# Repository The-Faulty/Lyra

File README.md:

# Lyra

**A SamD21 Based Rocket Deployment Altimeter**

This altimeter will be able to be used for single deployment events in mid to high power rocketry. A compact design was emphasized in order to allow for use in 24mm and larger body tubes, or attached to the parachute for a cable cutter or similar deployment method.

## Current State

As of right now, I am working on flight software with basic functionality. The original PCB design is filled with many flaws, however, I still included them for use as a reference. Plans have been made for a new version of the PCB to fix many, if not all, of the shortcomings my original design had. I believe I have found most of them, but one includes the difficulty of updating firmware and testing, which will inevitably lead to something being overlooked. Also to come are some pictures of the one prototype board that I have assembled. The changelog below is more to keep track of what I have or haven't tackled yet, so feel free to ignore it.

I have now successfully uploaded a version of the code to a Lyra board. One thing I did was replace the buzzer on the board with a bodged LED. This will allow for silent debugging and a guarantee that the lines are working. *This is the purpose of any digital writes to the buzzer pin.* The code that I uploaded ran until it attempted connection with the barometer in the setup. I will look further into the issue at a later point in time.

## The Bad, the Worse, and the Annoying

During my initial development of the Lyra pcb, I made some naive choices in terms of design, and overlooked other quality of life aspects which have led to many headaches during development. I'm going to go into some of the things that I have identified as issues in the current design or things I want to add in the next one.

The biggest issue that I made in the design of this pcb was not using a USB port. I figured that as long as I had the SWD I would be fine, but it just complicates development because I can't have the flash and SD card board attached at the same time. Another issue is lack of physical indicators. having LEDs on the power lines, pyro lines, and just attached to a GPIO pin would have helped a lot in diagnosing issues. Instead of using the BMP388, a barometer that I have used before and knew worked, I chose the MS5607 for Lyra. I don't remember why I made that choice, but the MS5607 has a few downsides compared to the BMP388. For one, there is no data ready register. This means that your code has to blindly wait for the reading to be completed, and then check back after. The libraries for using this sensor are also less tested than those for the BMP388. I also did not think very hard about the use of Lyra during an actual launch. I planned for the code to read a settings file from the SD card at launch, however, if I planned on using Lyra in multiple rockets or adjust settings on the go, I would have to bring a laptop. On the next itteration, one solution would be to use an oled shield, such as the adafruit feather oled, with a simple menu system for settings and readout. Finally, I wish I had broken out more pins to the daughter pcb. I didn't use all of the pins on the connector, and could have broken out I2C lines or similar for further prototyping.

## Changelog

Latest Changes:

**V0.2 - "Hands up, Don't Chute!"**

Notes: I think that most of the program is here, just need to do the loop logic. I also want to add data logging to the start of the flight.

- Fixed typo of `stateMacine` to `stateMachine`
- Fixed `state` being initialized as an integer instead of an instance of the `stateMachine` enum
- Fixed lack of function prototypes

- Changed `loop()` to use switch/case instead of `if else`
- Moved `readAlt()` to the start of if statement instead of in each case

- Added `ISDROGUE` and `ISAPOGEEDEPLOY` to user variables (I missed them in the last update)
- Added `DEPLOYALT` variable for setting the deployment altitude
- Added `SAVEDATA` boolean to toggle saving data to flash
- Added use of buzzer in `setup()` for indicating barometer found and setup complete
- Added `landed` case to `loop()`
- Added `rollPeriod` and `rollVelo` for use in velocity and acceleration calculations
- Added `calcAccel` for acceleration

**V0.1 - "No Function Junction"**

- Fixed variables being logged being out of order
- Fixed barometer code to use correct barometer model
- Fixed `readAlt()` function's for loop running until greater than the array's index
- Fixed not changing state from `startUp` to `idle` in setup

- Removed variable `rateLeng` and instead directly used the `rollAvg` array for vertical speed calculation

- Changed user-defined variables to be under define tags to allow usage in declaring array lengths

- Added vertical speed function (`getRate()`) and `avgRate` variable
- Added battery voltage function (`getBattVoltage()`)
- Added vertical speed to logging data
- Added `period` and `lastMillis` variables for tracking loop cycles
- Added majority of this ReadMe

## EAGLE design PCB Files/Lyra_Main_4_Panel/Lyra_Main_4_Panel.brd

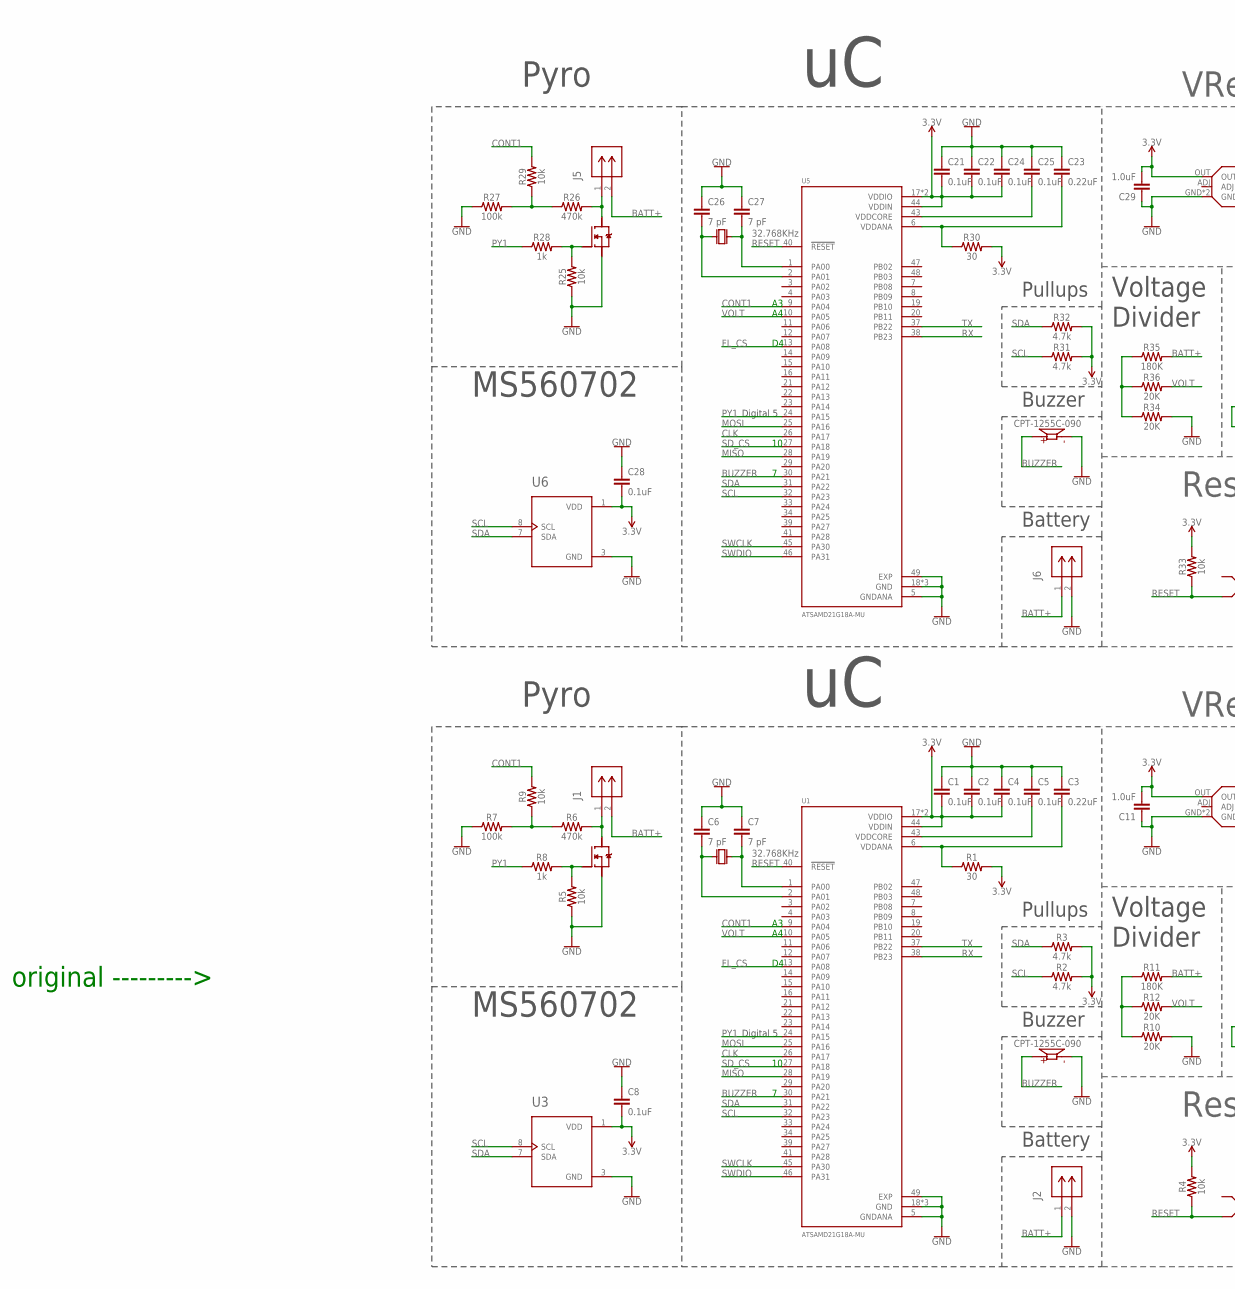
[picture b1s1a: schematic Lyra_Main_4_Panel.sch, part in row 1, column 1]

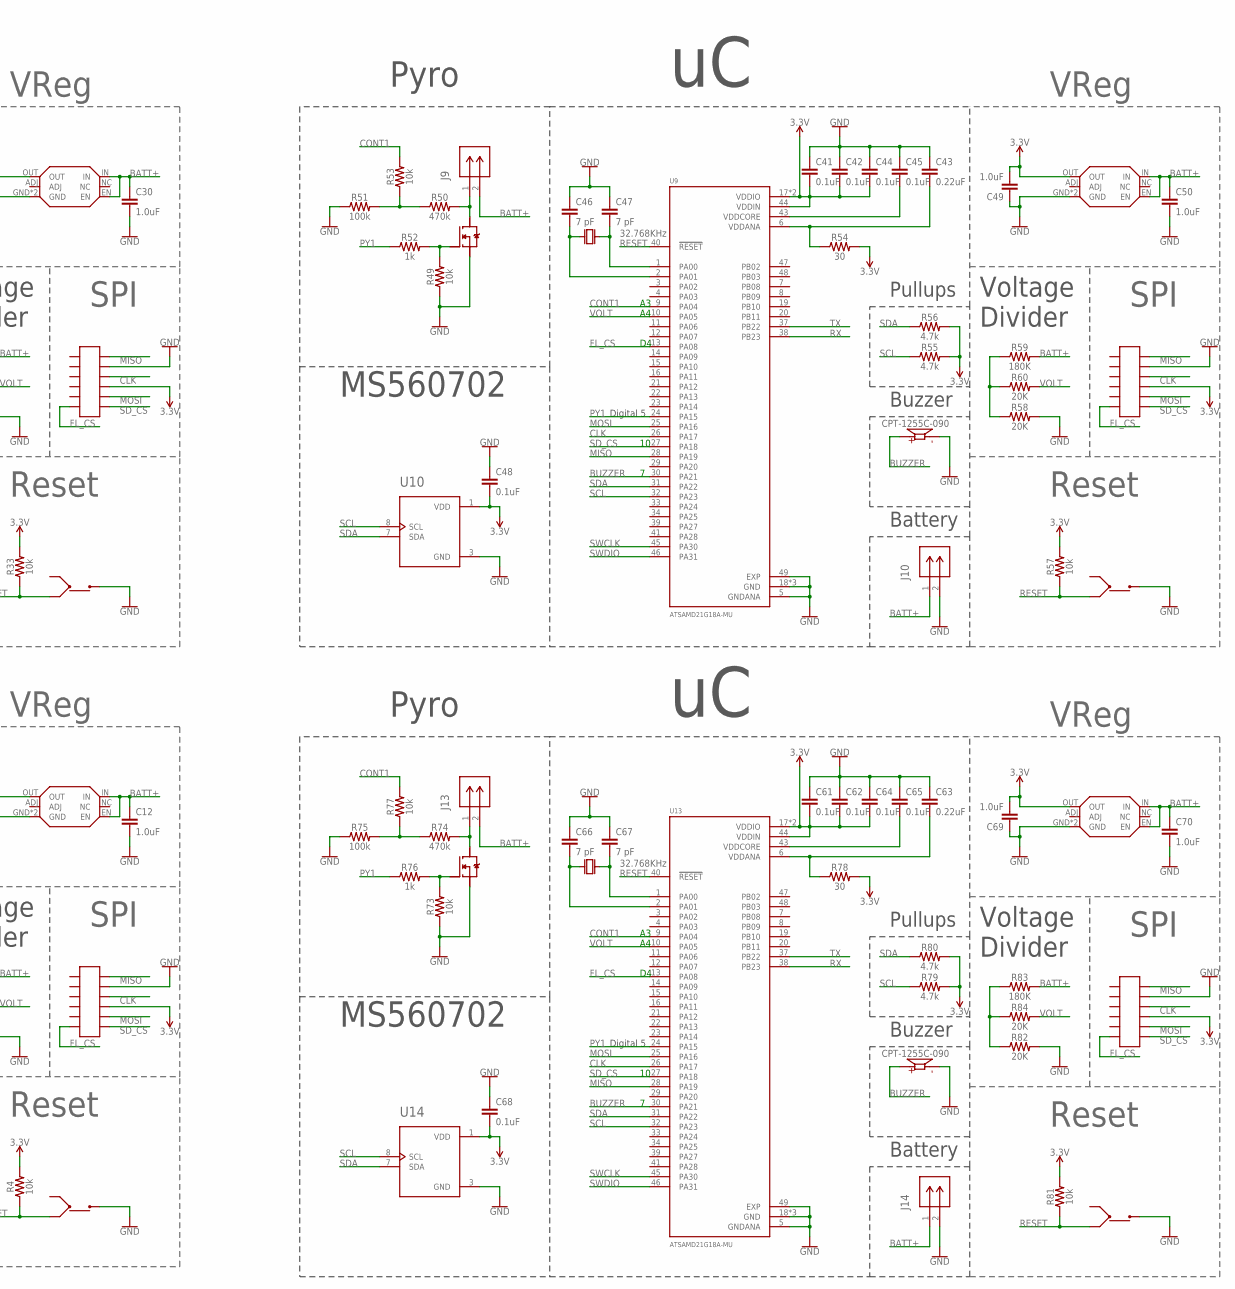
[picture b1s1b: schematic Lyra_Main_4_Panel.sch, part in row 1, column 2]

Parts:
C1, C2, C4, C5, C8, C21, C22, C24, C25, C28, C41, C42, C44, C45, C48, C61, C62, C64, C65, C68: 0.1uF; 0603
C3, C23, C43, C63: 0.22uF; 0603
C6, C7, C26, C27, C46, C47, C66, C67: 7 pF; 0402
C11, C12, C29, C30, C49, C50, C69, C70: 1.0uF; 0402
J1, J2, J5, J6, J9, J10, J13, J14: OSTVN02A150; CONN_OSTVN02A150_OST
LS2, LS3, LS5, LS7: CPT-1255C-090; CUI_CPT-1255C-090
R1, R30, R54, R78: 30; 0402
R2, R3, R31, R32, R55, R56, R79, R80: 4.7k; 0603
R4, R5, R9, R25, R29, R33, R49, R53, R57, R73, R77, R81: 10k; 0402
R6, R26, R50, R74: 470k; 0402
R7, R27, R51, R75: 100k; 0402
R8, R28, R52, R76: 1k; 0402
R10, R12, R34, R36, R58, R60, R82, R84: 20K; 0402
R11, R35, R59, R83: 180K; 0402
U1, U5, U9, U13: ATSAMD21G18A-MU; QFN50P700X700X90-49N
U3, U6, U10, U14: MS860702BA01-50; TE_MS860702BA01-50
U$1, U$12, U$22, U$32: 32.768KHz; FC-135
U$2, U$11, U$21, U$31: IRLHM630PBF
U$3, U$13, U$23, U$33: NCP718AMT330TBG; NCP718BMT330TBG
U$4, U$14, U$24, U$34: BUTTON
U$5, U$15, U$25, U$35: 12POS_SOCKET

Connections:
3.3V: C1.2, C2.2, C4.2, C8.2, C11.2, C21.2, C22.2, C24.2, C28.2, C29.2, C41.2, C42.2, C44.2, C48.2, C49.2, C61.2, C62.2, C64.2, C68.2, C69.2, R1.2, R2.2, R3.2, R4.2, R30.2, R31.2, R32.2, R33.2, R54.2, R55.2, R56.2, R57.2, R78.2, R79.2, R80.2, R81.2, U1.17 (VDDIO), U1.36 (VDDIO), U1.44 (VDDIN), U3.1 (VDD), U5.17 (VDDIO), U5.36 (VDDIO), U5.44 (VDDIN), U6.1 (VDD), U9.17 (VDDIO), U9.36 (VDDIO), U9.44 (VDDIN), U10.1 (VDD), U13.17 (VDDIO), U13.36 (VDDIO), U13.44 (VDDIN), U14.1 (VDD), U$3.OUT, U$5.P$9, U$13.OUT, U$15.P$9, U$23.OUT, U$25.P$9, U$33.OUT, U$35.P$9
BATT+: C12.1, C30.1, C50.1, C70.1, J1.2, J2.1, J5.2, J6.1, J9.2, J10.1, J13.2, J14.1, R11.2, R35.2, R59.2, R83.2, U$3.EN, U$3.IN, U$13.EN, U$13.IN, U$23.EN, U$23.IN, U$33.EN, U$33.IN
BUZZER: LS2.P, LS3.P, LS5.P, LS7.P, U1.30 (PA21), U5.30 (PA21), U9.30 (PA21), U13.30 (PA21)
CLK: U1.26 (PA17), U5.26 (PA17), U9.26 (PA17), U13.26 (PA17), U$5.P$10, U$15.P$10, U$25.P$10, U$35.P$10
CONT1: R9.2, R29.2, R53.2, R77.2, U1.9 (PA04), U5.9 (PA04), U9.9 (PA04), U13.9 (PA04)
FL_CS: U1.13 (PA08), U5.13 (PA08), U9.13 (PA08), U13.13 (PA08), U$5.P$6, U$15.P$6, U$25.P$6, U$35.P$6
GND: C1.1, C2.1, C3.1, C4.1, C5.1, C6.1, C7.1, C8.1, C11.1, C12.2, C21.1, C22.1, C23.1, C24.1, C25.1, C26.1, C27.1, C28.1, C29.1, C30.2, C41.1, C42.1, C43.1, C44.1, C45.1, C46.1, C47.1, C48.1, C49.1, C50.2, C61.1, C62.1, C63.1, C64.1, C65.1, C66.1, C67.1, C68.1, C69.1, C70.2, J2.2, J6.2, J10.2, J14.2, LS2.N, LS3.N, LS5.N, LS7.N, R5.1, R7.1, R10.2, R25.1, R27.1, R34.2, R49.1, R51.1, R58.2, R73.1, R75.1, R82.2, U1.5 (GNDANA), U1.18 (GND), U1.35 (GND), U1.42 (GND), U1.49 (EXP), U3.3 (GND), U5.5 (GNDANA), U5.18 (GND), U5.35 (GND), U5.42 (GND), U5.49 (EXP), U6.3 (GND), U9.5 (GNDANA), U9.18 (GND), U9.35 (GND), U9.42 (GND), U9.49 (EXP), U10.3 (GND), U13.5 (GNDANA), U13.18 (GND), U13.35 (GND), U13.42 (GND), U13.49 (EXP), U14.3 (GND), U$2.P$2, U$2.P$3, U$2.P$4, U$3.GND, U$3.P$7 (GND), U$4.4 (OUT), U$5.P$11, U$11.P$2, U$11.P$3, U$11.P$4, U$13.GND, U$13.P$7 (GND), U$14.4 (OUT), U$15.P$11, U$21.P$2, U$21.P$3, U$21.P$4, U$23.GND, U$23.P$7 (GND), U$24.4 (OUT), U$25.P$11, U$31.P$2, U$31.P$3, U$31.P$4, U$33.GND, U$33.P$7 (GND), U$34.4 (OUT), U$35.P$11
MISO: U1.28 (PA19), U5.28 (PA19), U9.28 (PA19), U13.28 (PA19), U$5.P$12, U$15.P$12, U$25.P$12, U$35.P$12
MOSI: U1.25 (PA16), U5.25 (PA16), U9.25 (PA16), U13.25 (PA16), U$5.P$8, U$15.P$8, U$25.P$8, U$35.P$8
unnamed: C7.2, U1.1 (PA00), U$1.P$2
unnamed: J1.1, R6.2, U$2.P$5, U$2.P$6, U$2.P$7, U$2.P$8, U$2.P$9
unnamed: R5.2, R8.2, U$2.P$1
unnamed: C6.2, U1.2 (PA01), U$1.P$1
unnamed: R6.1, R7.2, R9.1
unnamed: R10.1, R11.1, R12.1
unnamed: C5.2, U1.43 (VDDCORE)
unnamed: C3.2, R1.1, U1.6 (VDDANA)
unnamed: J5.1, R26.2, U$11.P$5, U$11.P$6, U$11.P$7, U$11.P$8, U$11.P$9
unnamed: R25.2, R28.2, U$11.P$1
unnamed: R26.1, R27.2, R29.1
unnamed: C27.2, U5.1 (PA00), U$12.P$2
unnamed: C26.2, U5.2 (PA01), U$12.P$1
unnamed: C25.2, U5.43 (VDDCORE)
unnamed: C23.2, R30.1, U5.6 (VDDANA)
unnamed: R34.1, R35.1, R36.1
unnamed: J9.1, R50.2, U$21.P$5, U$21.P$6, U$21.P$7, U$21.P$8, U$21.P$9
unnamed: R49.2, R52.2, U$21.P$1
unnamed: R50.1, R51.2, R53.1
unnamed: C47.2, U9.1 (PA00), U$22.P$2
unnamed: C46.2, U9.2 (PA01), U$22.P$1
unnamed: C45.2, U9.43 (VDDCORE)
unnamed: C43.2, R54.1, U9.6 (VDDANA)
unnamed: R58.1, R59.1, R60.1
unnamed: J13.1, R74.2, U$31.P$5, U$31.P$6, U$31.P$7, U$31.P$8, U$31.P$9
unnamed: R73.2, R76.2, U$31.P$1
unnamed: R74.1, R75.2, R77.1
unnamed: C67.2, U13.1 (PA00), U$32.P$2
unnamed: C66.2, U13.2 (PA01), U$32.P$1
unnamed: C65.2, U13.43 (VDDCORE)
unnamed: C63.2, R78.1, U13.6 (VDDANA)
unnamed: R82.1, R83.1, R84.1
PY1: R8.1, R28.1, R52.1, R76.1, U1.24 (PA15), U5.24 (PA15), U9.24 (PA15), U13.24 (PA15)
RESET: R4.1, R33.1, R57.1, R81.1, U1.40 (!RESET), U5.40 (!RESET), U9.40 (!RESET), U13.40 (!RESET), U$4.2 (IN(2)), U$14.2 (IN(2)), U$24.2 (IN(2)), U$34.2 (IN(2))
RX: U1.38 (PB23), U5.38 (PB23), U9.38 (PB23), U13.38 (PB23)
SCL: R2.1, R31.1, R55.1, R79.1, U1.32 (PA23), U3.8 (SCL), U5.32 (PA23), U6.8 (SCL), U9.32 (PA23), U10.8 (SCL), U13.32 (PA23), U14.8 (SCL)
SDA: R3.1, R32.1, R56.1, R80.1, U1.31 (PA22), U3.7 (SDA), U5.31 (PA22), U6.7 (SDA), U9.31 (PA22), U10.7 (SDA), U13.31 (PA22), U14.7 (SDA)
SD_CS: U1.27 (PA18), U5.27 (PA18), U9.27 (PA18), U13.27 (PA18), U$5.P$7, U$15.P$7, U$25.P$7, U$35.P$7
SWCLK: U1.45 (PA30), U5.45 (PA30), U9.45 (PA30), U13.45 (PA30)
SWDIO: U1.46 (PA31), U5.46 (PA31), U9.46 (PA31), U13.46 (PA31)
TX: U1.37 (PB22), U5.37 (PB22), U9.37 (PB22), U13.37 (PB22)
VOLT: R12.2, R36.2, R60.2, R84.2, U1.10 (PA05), U5.10 (PA05), U9.10 (PA05), U13.10 (PA05)

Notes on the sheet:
Pyro
Buzzer
Battery
MS560702
Pullups
VReg
SPI
Reset
Digital 5
Voltage Divider
original --------->

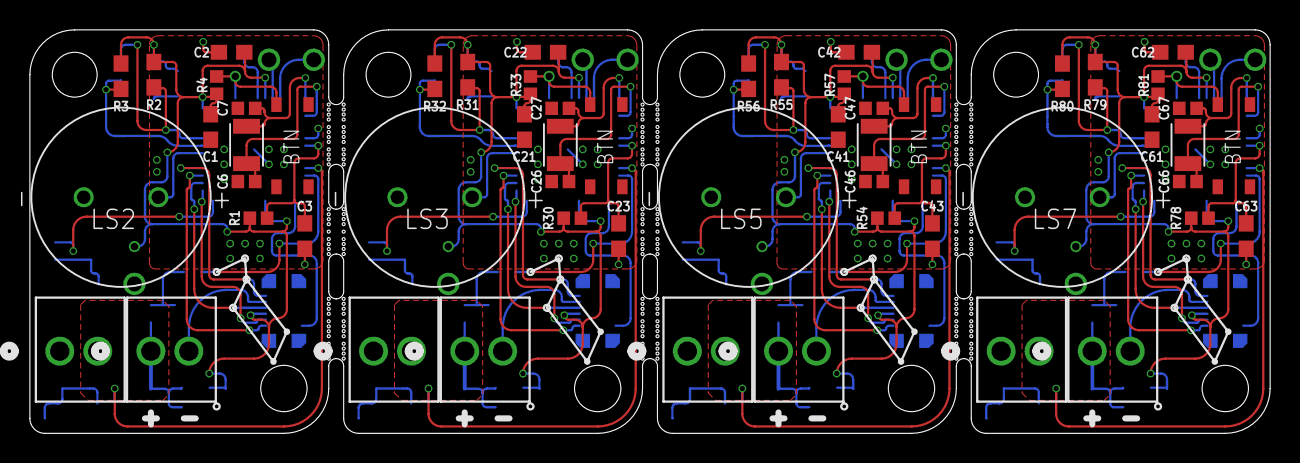
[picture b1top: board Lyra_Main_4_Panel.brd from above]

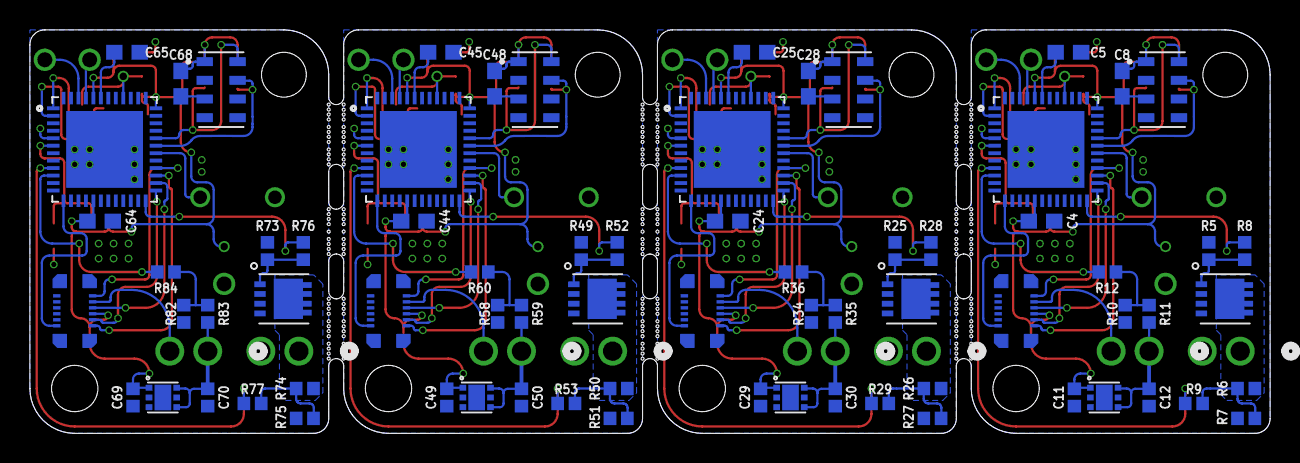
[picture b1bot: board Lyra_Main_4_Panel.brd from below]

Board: 2 copper layers, 83.0 x 27.0 mm, 128 parts (72 on the bottom side), 51 nets.

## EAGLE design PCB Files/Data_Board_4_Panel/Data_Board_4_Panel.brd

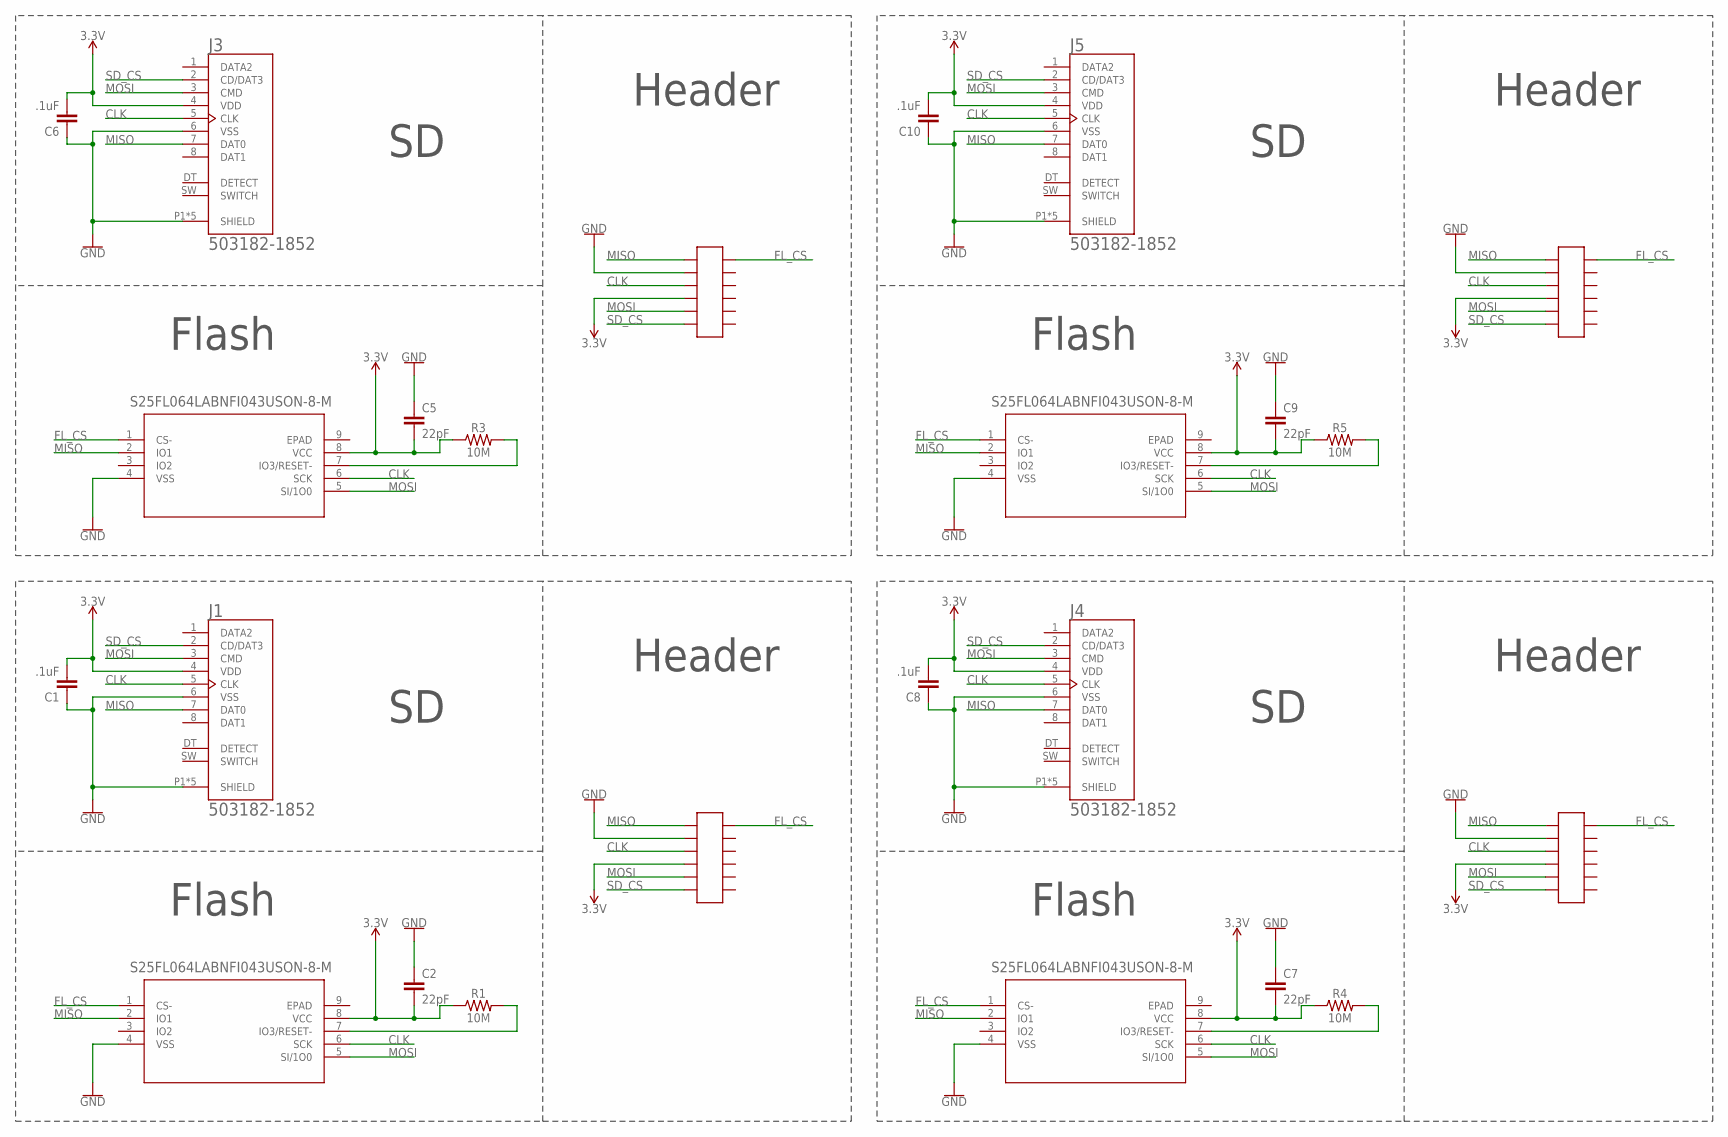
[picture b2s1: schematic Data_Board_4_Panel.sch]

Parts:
C1, C6, C8, C10: .1uF; 0603
C2, C5, C7, C9: 22pF; 0603
J1, J3, J4, J5: 503182-1852; MOLEX_503182-1852
R1, R3, R4, R5: 10M; 0603
U1, U3, U4, U5: S25FL064LABNFI043USON-8-M; USON-8-M
U$1, U$3, U$4, U$5: 12POS_HEADER

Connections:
3.3V: C1.2, C2.2, C5.2, C6.2, C7.2, C8.2, C9.2, C10.2, J1.4 (VDD), J3.4 (VDD), J4.4 (VDD), J5.4 (VDD), R1.1, R3.1, R4.1, R5.1, U1.8 (VCC), U3.8 (VCC), U4.8 (VCC), U5.8 (VCC), U$1.P$4, U$3.P$4, U$4.P$4, U$5.P$4
CLK: J1.5 (CLK), J3.5 (CLK), J4.5 (CLK), J5.5 (CLK), U1.6 (SCK), U3.6 (SCK), U4.6 (SCK), U5.6 (SCK), U$1.P$3, U$3.P$3, U$4.P$3, U$5.P$3
FL_CS: U1.1 (CS-), U3.1 (CS-), U4.1 (CS-), U5.1 (CS-), U$1.P$12, U$3.P$12, U$4.P$12, U$5.P$12
GND: C1.1, C2.1, C5.1, C6.1, C7.1, C8.1, C9.1, C10.1, J1.6 (VSS), J1.P1 (SHIELD), J1.P2 (SHIELD), J1.P3 (SHIELD), J1.P4 (SHIELD), J1.P5 (SHIELD), J3.6 (VSS), J3.P1 (SHIELD), J3.P2 (SHIELD), J3.P3 (SHIELD), J3.P4 (SHIELD), J3.P5 (SHIELD), J4.6 (VSS), J4.P1 (SHIELD), J4.P2 (SHIELD), J4.P3 (SHIELD), J4.P4 (SHIELD), J4.P5 (SHIELD), J5.6 (VSS), J5.P1 (SHIELD), J5.P2 (SHIELD), J5.P3 (SHIELD), J5.P4 (SHIELD), J5.P5 (SHIELD), U1.4 (VSS), U3.4 (VSS), U4.4 (VSS), U5.4 (VSS), U$1.P$2, U$3.P$2, U$4.P$2, U$5.P$2
MISO: J1.7 (DAT0), J3.7 (DAT0), J4.7 (DAT0), J5.7 (DAT0), U1.2 (IO1), U3.2 (IO1), U4.2 (IO1), U5.2 (IO1), U$1.P$1, U$3.P$1, U$4.P$1, U$5.P$1
MOSI: J1.3 (CMD), J3.3 (CMD), J4.3 (CMD), J5.3 (CMD), U1.5 (SI/1O0), U3.5 (SI/1O0), U4.5 (SI/1O0), U5.5 (SI/1O0), U$1.P$5, U$3.P$5, U$4.P$5, U$5.P$5
unnamed: R3.2, U3.7 (IO3/RESET-)
unnamed: R4.2, U4.7 (IO3/RESET-)
unnamed: R5.2, U5.7 (IO3/RESET-)
unnamed: R1.2, U1.7 (IO3/RESET-)
SD_CS: J1.2 (CD/DAT3), J3.2 (CD/DAT3), J4.2 (CD/DAT3), J5.2 (CD/DAT3), U$1.P$6, U$3.P$6, U$4.P$6, U$5.P$6

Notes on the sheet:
Flash
Header

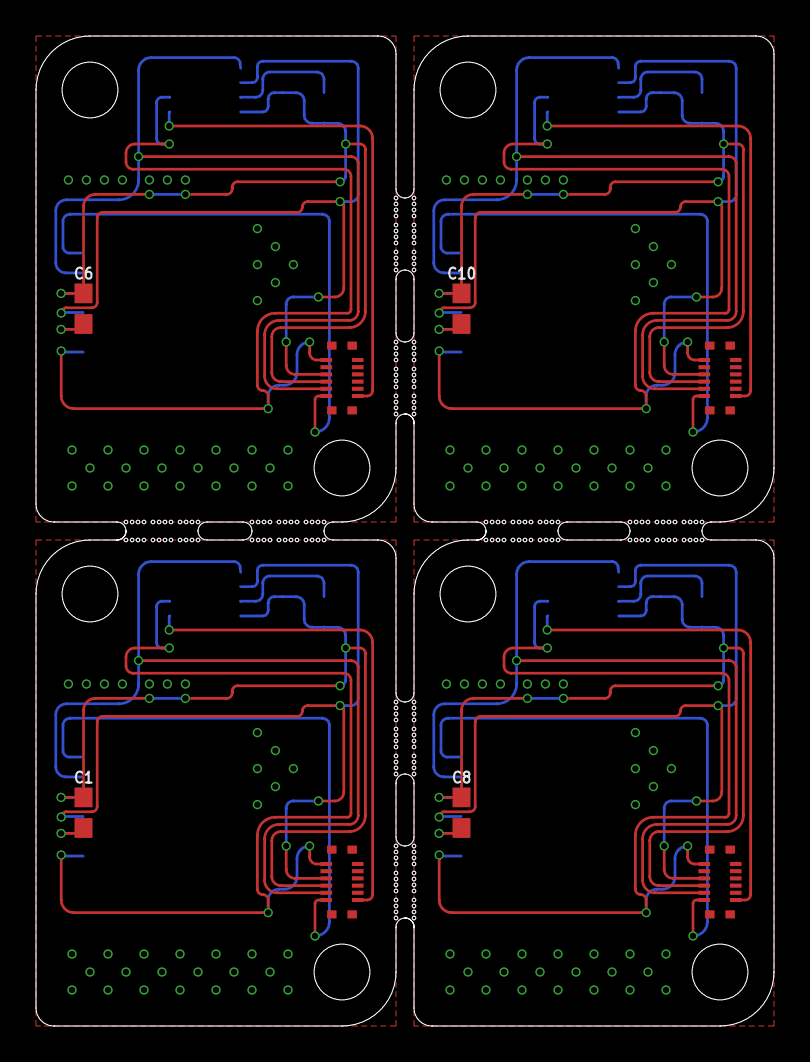
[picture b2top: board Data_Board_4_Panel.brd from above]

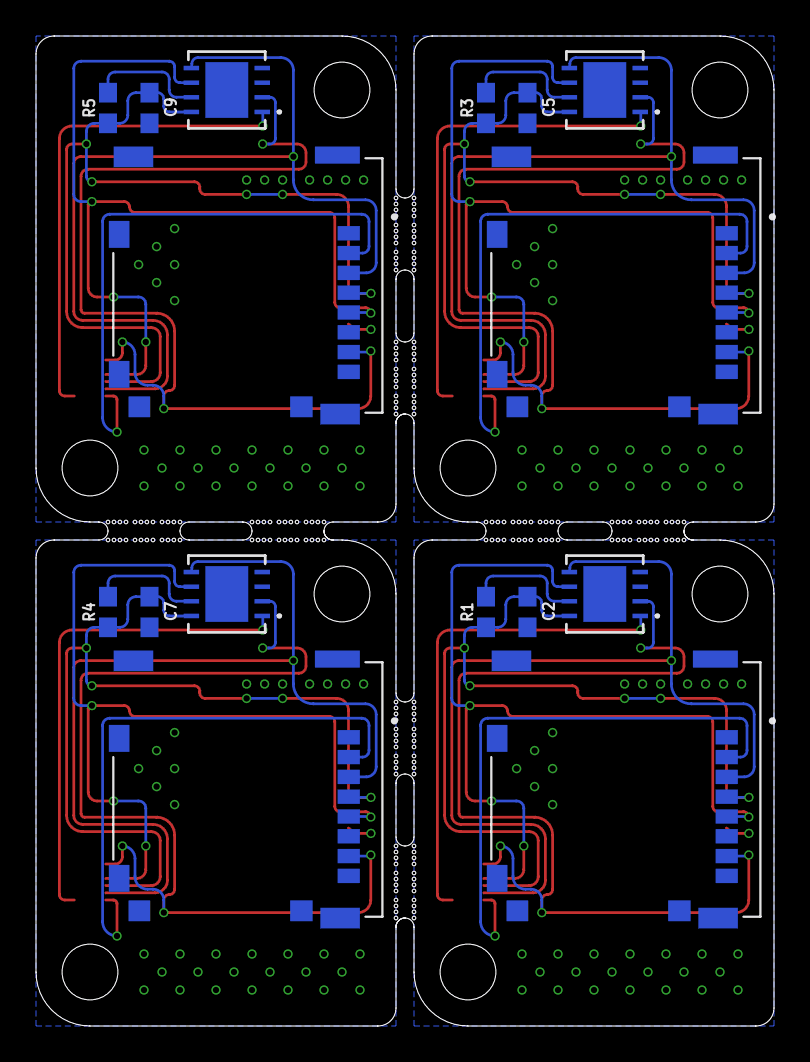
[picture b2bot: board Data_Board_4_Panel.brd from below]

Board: 2 copper layers, 41.0 x 55.0 mm, 24 parts (16 on the bottom side), 11 nets.

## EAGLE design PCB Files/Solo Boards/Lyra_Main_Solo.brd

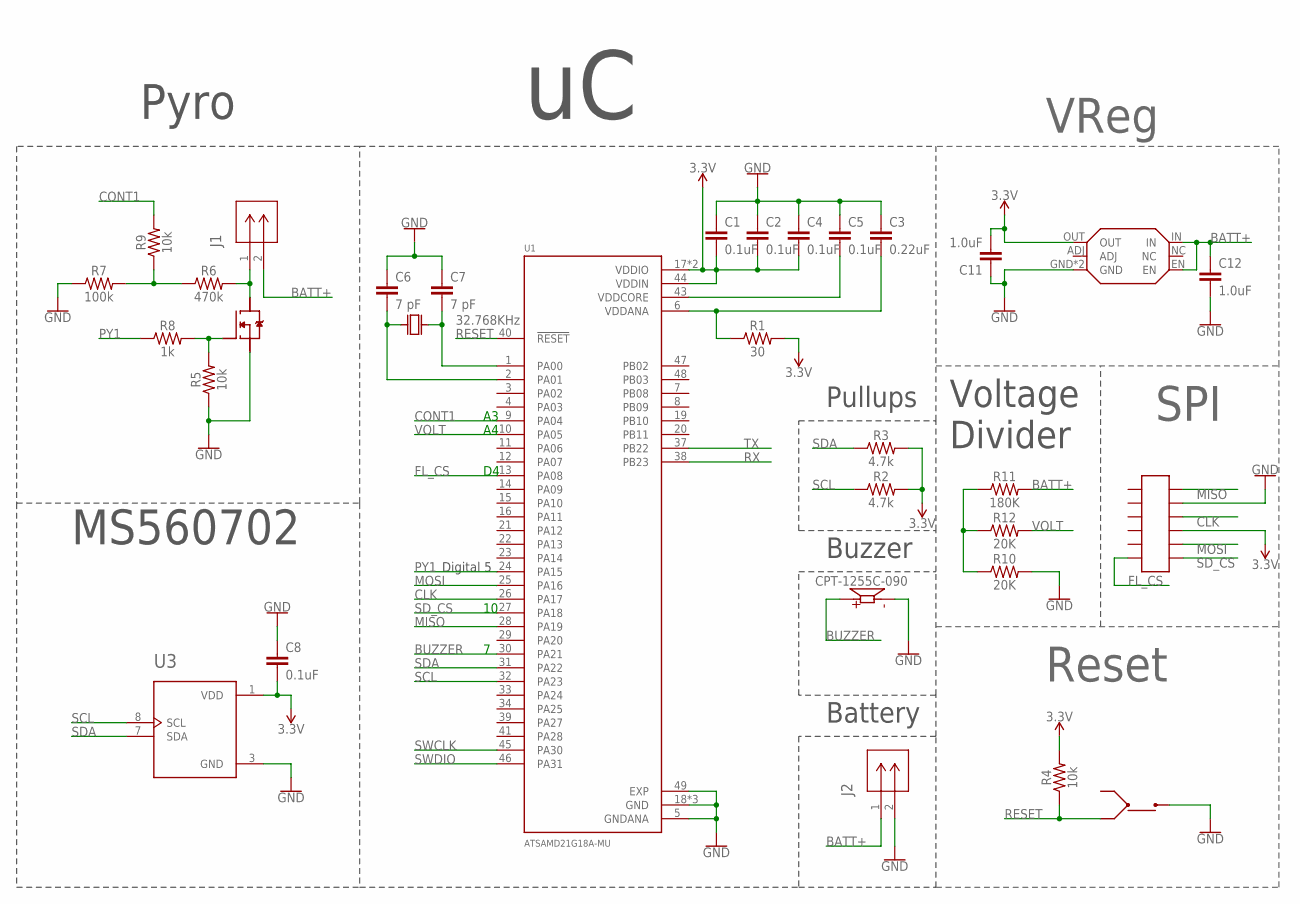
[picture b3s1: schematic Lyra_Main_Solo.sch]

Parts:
C1, C2, C4, C5, C8: 0.1uF; 0603
C3: 0.22uF; 0603
C6, C7: 7 pF; 0402
C11, C12: 1.0uF; 0402
J1, J2: OSTVN02A150; CONN_OSTVN02A150_OST
LS2: CPT-1255C-090; CUI_CPT-1255C-090
R1: 30; 0402
R2, R3: 4.7k; 0603
R4, R5, R9: 10k; 0402
R6: 470k; 0402
R7: 100k; 0402
R8: 1k; 0402
R10, R12: 20K; 0402
R11: 180K; 0402
U1: ATSAMD21G18A-MU; QFN50P700X700X90-49N
U3: MS860702BA01-50; TE_MS860702BA01-50
U$1: 32.768KHz; FC-135
U$2: IRLHM630PBF
U$3: NCP718AMT330TBG; NCP718BMT330TBG
U$4: BUTTON
U$5: 12POS_SOCKET

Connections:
3.3V: C1.2, C2.2, C4.2, C8.2, C11.2, R1.2, R2.2, R3.2, R4.2, U1.17 (VDDIO), U1.36 (VDDIO), U1.44 (VDDIN), U3.1 (VDD), U$3.OUT, U$5.P$9
BATT+: C12.1, J1.2, J2.1, R11.2, U$3.EN, U$3.IN
BUZZER: LS2.P, U1.30 (PA21)
CLK: U1.26 (PA17), U$5.P$10
CONT1: R9.2, U1.9 (PA04)
FL_CS: U1.13 (PA08), U$5.P$6
GND: C1.1, C2.1, C3.1, C4.1, C5.1, C6.1, C7.1, C8.1, C11.1, C12.2, J2.2, LS2.N, R5.1, R7.1, R10.2, U1.5 (GNDANA), U1.18 (GND), U1.35 (GND), U1.42 (GND), U1.49 (EXP), U3.3 (GND), U$2.P$2, U$2.P$3, U$2.P$4, U$3.GND, U$3.P$7 (GND), U$4.4 (OUT), U$5.P$11
MISO: U1.28 (PA19), U$5.P$12
MOSI: U1.25 (PA16), U$5.P$8
unnamed: C7.2, U1.1 (PA00), U$1.P$2
unnamed: J1.1, R6.2, U$2.P$5, U$2.P$6, U$2.P$7, U$2.P$8, U$2.P$9
unnamed: R5.2, R8.2, U$2.P$1
unnamed: C6.2, U1.2 (PA01), U$1.P$1
unnamed: R6.1, R7.2, R9.1
unnamed: R10.1, R11.1, R12.1
unnamed: C5.2, U1.43 (VDDCORE)
unnamed: C3.2, R1.1, U1.6 (VDDANA)
PY1: R8.1, U1.24 (PA15)
RESET: R4.1, U1.40 (!RESET), U$4.2 (IN(2))
RX: U1.38 (PB23)
SCL: R2.1, U1.32 (PA23), U3.8 (SCL)
SDA: R3.1, U1.31 (PA22), U3.7 (SDA)
SD_CS: U1.27 (PA18), U$5.P$7
SWCLK: U1.45 (PA30)
SWDIO: U1.46 (PA31)
TX: U1.37 (PB22)
VOLT: R12.2, U1.10 (PA05)

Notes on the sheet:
Pyro
Buzzer
Battery
MS560702
Pullups
VReg
SPI
Reset
Digital 5
Voltage Divider

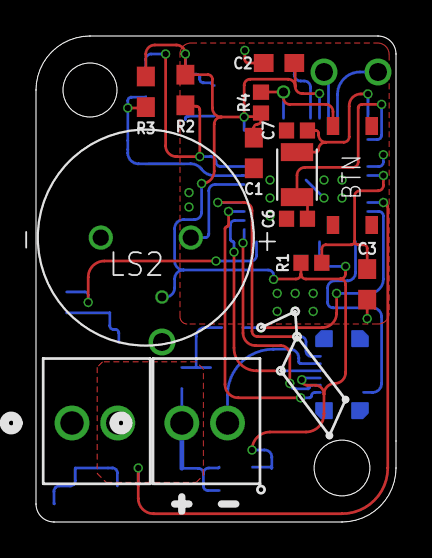
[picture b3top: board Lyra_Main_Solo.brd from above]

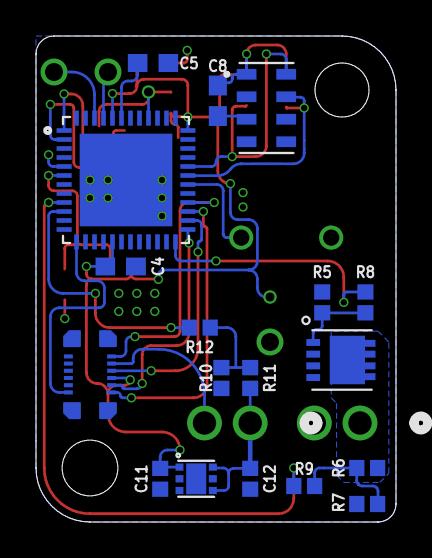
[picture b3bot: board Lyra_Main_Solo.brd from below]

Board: 2 copper layers, 20.0 x 27.0 mm, 32 parts (18 on the bottom side), 23 nets.

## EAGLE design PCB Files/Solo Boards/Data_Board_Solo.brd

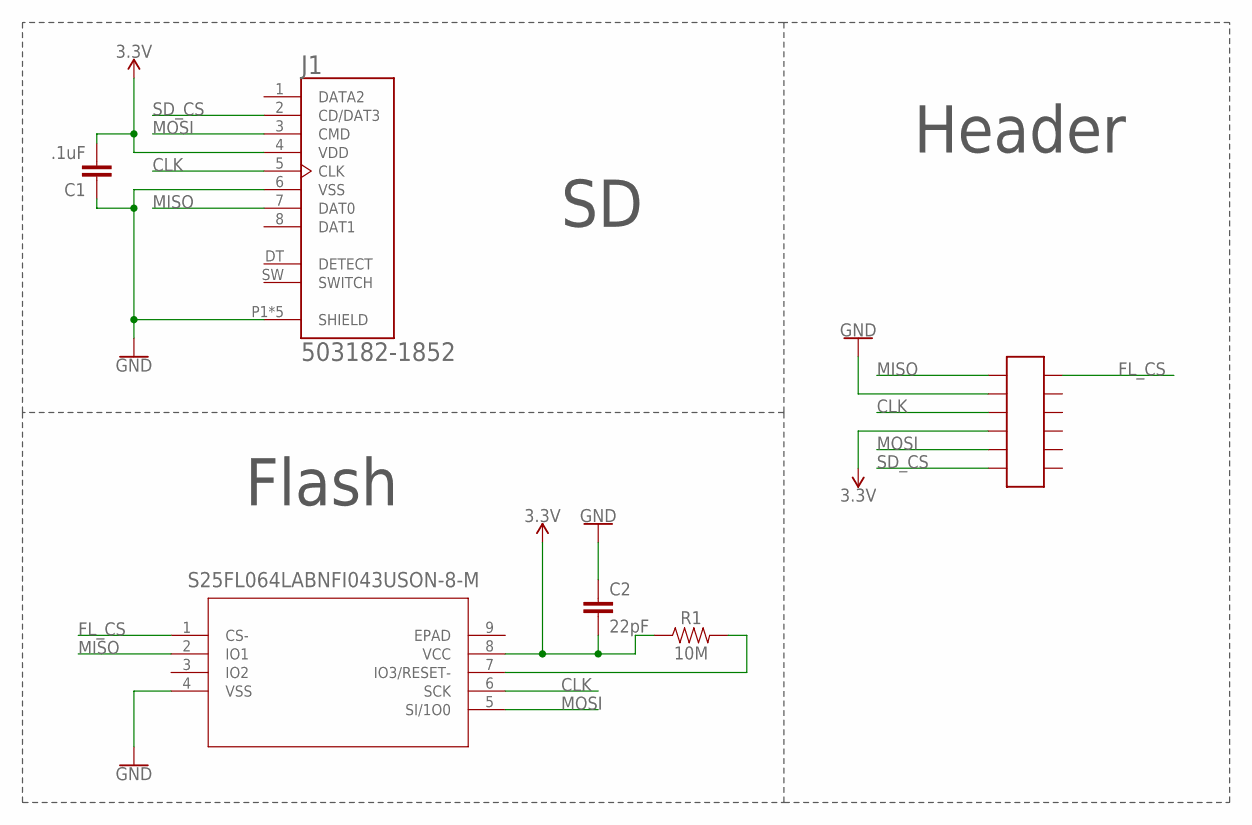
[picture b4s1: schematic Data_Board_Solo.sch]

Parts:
C1: .1uF; 0603
C2: 22pF; 0603
J1: 503182-1852; MOLEX_503182-1852
R1: 10M; 0603
U1: S25FL064LABNFI043USON-8-M; USON-8-M
U$1: 12POS_HEADER

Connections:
3.3V: C1.2, C2.2, J1.4 (VDD), R1.1, U1.8 (VCC), U$1.P$4
CLK: J1.5 (CLK), U1.6 (SCK), U$1.P$3
FL_CS: U1.1 (CS-), U$1.P$12
GND: C1.1, C2.1, J1.6 (VSS), J1.P1 (SHIELD), J1.P2 (SHIELD), J1.P3 (SHIELD), J1.P4 (SHIELD), J1.P5 (SHIELD), U1.4 (VSS), U$1.P$2
MISO: J1.7 (DAT0), U1.2 (IO1), U$1.P$1
MOSI: J1.3 (CMD), U1.5 (SI/1O0), U$1.P$5
unnamed: R1.2, U1.7 (IO3/RESET-)
SD_CS: J1.2 (CD/DAT3), U$1.P$6

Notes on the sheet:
Flash
Header

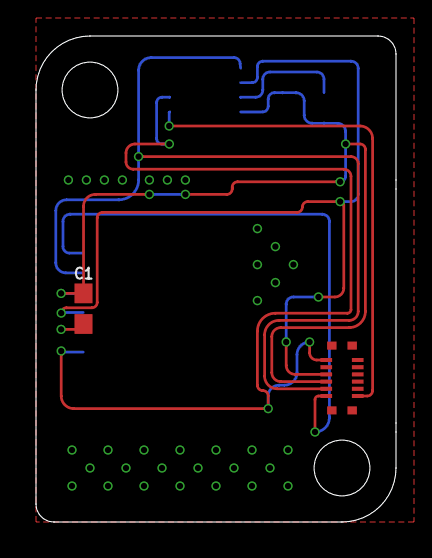
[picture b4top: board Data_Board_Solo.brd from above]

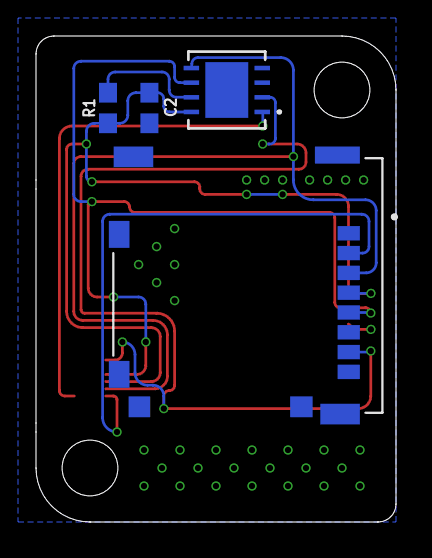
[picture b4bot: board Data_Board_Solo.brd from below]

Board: 2 copper layers, 20.0 x 27.0 mm, 6 parts (4 on the bottom side), 8 nets.

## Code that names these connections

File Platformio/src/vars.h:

#include <Wire.h>
#include <SPI.h>
#include <MS5x.h>
#include <SPIMemory.h>
#include <SD.h>
#include <SDU.h>
#include <errors.h>

#define CONT1 A3
#define VOLT A4
#define FL_CS 4
#define PY1 5
#define BUZZER 7
#define SD_CS 10

//User defined variables
#define MINALT 200                                                          //Minimum altitude for flight detection
#define ROLLAVGLENG 10                                                      //Defines the length of the roling average
#define ISDROGUE false                                                      //Set true if using Lyra to deploy drogue chutes
#define ISAPOGEEDEPLOY false                                                //Set true if you want Lyra to deploy parachutes at apogee
#define DEPLOYALT 500                                                       //Sets the deployment altitude, ignore if using apogee deployment
#define SAVEDATA false                                                      //Mainly for testing purposes

MS5x baro(&Wire);
SPIFlash flash;
File myFile;

int period;                                                                 //Period between program loops
int lastMillis;                                                             //Last time loop was run
int rollPeriod[ROLLAVGLENG];                                                //Period between readings for velocity purposes
int lastReadingMillis;                                                      //Last time a reading was taken

float gndPres;                                                              //Pressure at the launch site ground
float curAlt;                                                               //Current altitude
float curPress;                                                             //Current pressure
float rollAvg[ROLLAVGLENG];                                                 //Used to take a rolling average of altitude data
float rollVelo[ROLLAVGLENG - 1];                                            //Used for acceleration calculations

float maxAlt;                                                               //Stores the max altitude 
float avgAlt;                                                               //Altitude after using the rolling average
float avgRate;                                                              //Average Vertical speed
float avgAccel;                                                             //Average vertical acceleration
int rollIndex = 0;                                                          //Used to loop through the 
int timesLessThan = 0;                                                      //Used to ensure apogee has been reached, when over 10

uint32_t flashIndex = 0;                                                    //Index where to write data to flash

//Function Prototypes
void readAlt();
void calcRate();
void calcAccel();
void logData();
bool isApogee();
byte getBattVoltage();

enum stateMachine {                                                         //State machine 
  startUp,
  idle,
  liftOff,
  burnOut,
  apogee,
  descent,
  drogue,
  mains,
  landed
};
stateMachine state;

#pragma pack(1)                                                             //tells compiler to pack the variables together with no weird spacing issues that there would otherwise be

struct LoggerVars {                                                         //Struct for data logging
  int pressure;
  int alt;
  int filtAlt;
  int rate;
  int accel;
  byte curState;
  byte battVolt;
  uint32_t time;
};

union Logger {
  LoggerVars vars;
  char raw[sizeof(LoggerVars)];
};

#pragma pack(0)                                                             //compiler can go back to normal

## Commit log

2022-02-26 Initial commit
    PCB files and early code
    Plenty of work to be done on software end. Possible PCB v2 to improve on many of the weak points of v1 design.
2022-03-08 V0.1 - "No Function Junction"
    Just minor additions to the code as well as fixes and lots of thinking to do.
2022-03-08 Updated .gitattributes
2022-03-10 "School work"
2022-03-10 More testing
2022-03-15 Mainly Readme updates
2022-03-16 I don't remember what I changed
2022-03-21 Acceleration function added and logging updated
2022-03-21 Update main.cpp
    Quick syntax fix
2022-03-22 Quick Fix: Added rollVelo into calcRate function

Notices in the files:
parts and their libraries:
SparkFun-Capacitors: Licensing: Creative Commons ShareAlike 4.0 International - https://creativecommons.org/licenses/by-sa/4.0
COPYRIGHT: Copyright (C) 2018 Accelerated Designs. All rights reserved
